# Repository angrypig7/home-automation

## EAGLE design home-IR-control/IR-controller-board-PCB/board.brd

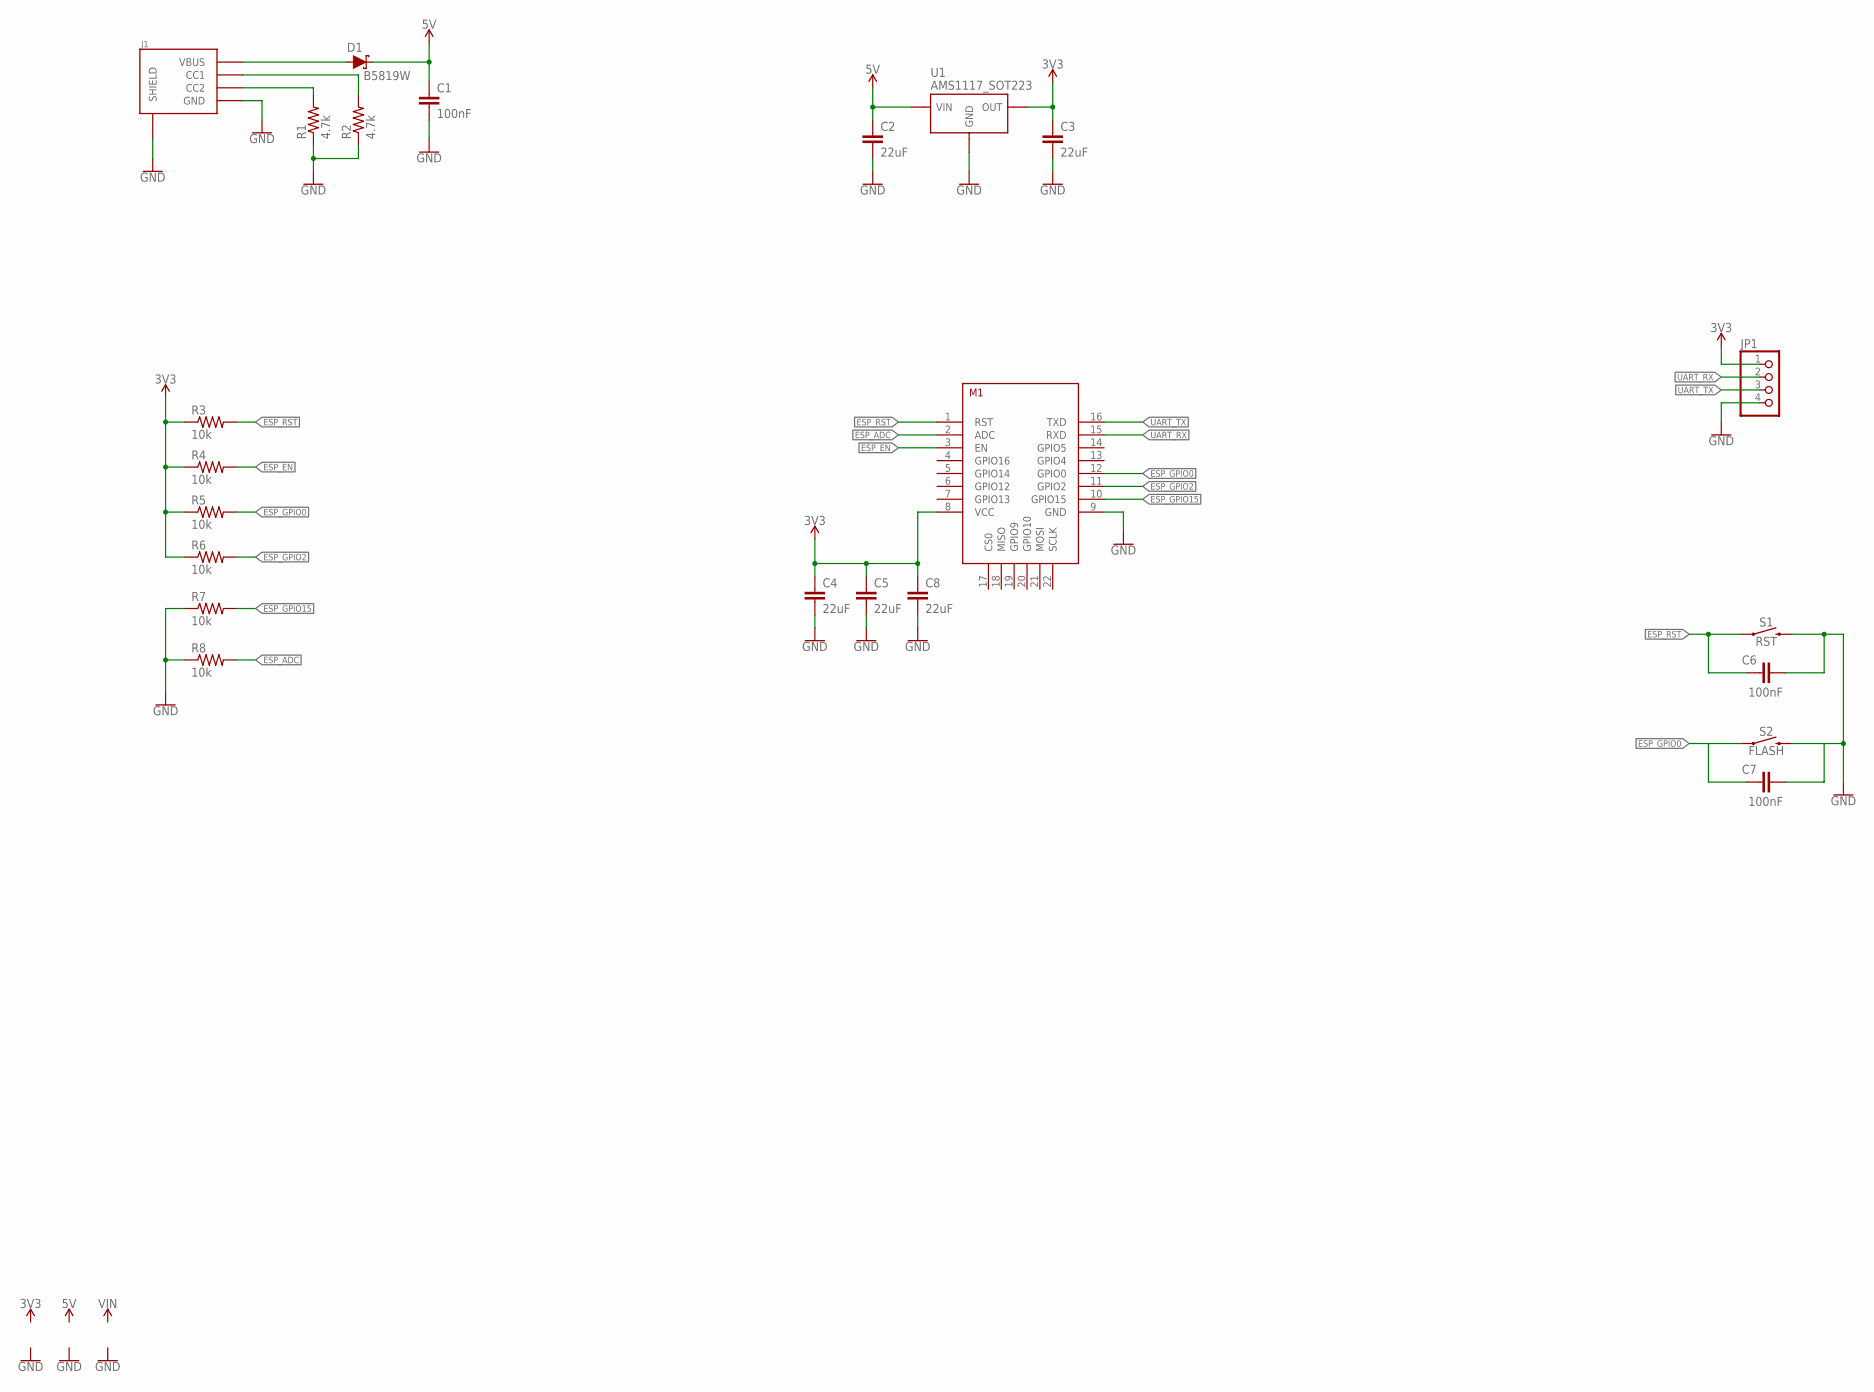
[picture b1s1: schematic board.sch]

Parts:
C1, C6, C7: 100nF; C0402; LCSC C1525
C2, C3, C4, C5, C8: 22uF; C0805; LCSC C45783
D1: B5819W; SOD-123; LCSC C8598
J1: USB-TYPE-C-31-M-17
JP1: PINHD-1X4; 1X04
M1: ESP8266-12E; ESP8266-ESP12E
R1, R2: 4.7k; R0402; LCSC C25900
R3, R4, R5, R6, R7, R8: 10k; R0402
S1: RST; TACTILE_SWITCH_SMD_3.0X4.0MM; LCSC C720477
S2: FLASH; TACTILE_SWITCH_SMD_3.0X4.0MM; LCSC C720477
U1: AMS1117_SOT223; SOT-223; LCSC C6186

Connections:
3V3: C3.1, C4.1, C5.1, C8.1, JP1.1, M1.8 (VCC), R3.1, R4.1, R5.1, R6.1, U1.2 (OUT), U1.4 (OUT)
5V: C1.1, C2.1, D1.C, U1.3 (VIN)
5V_IN1: D1.A, J1.VBUS, J1.VBUS_2 (VBUS)
ESP_ADC: M1.2 (ADC), R8.2
ESP_EN: M1.3 (EN), R4.2
ESP_GPIO0: M1.12 (GPIO0), R5.2, S2.1
ESP_GPIO2: M1.11 (GPIO2), R6.2
ESP_GPIO15: M1.10 (GPIO15), R7.2
ESP_RST: C6.1, M1.1 (RST), R3.2, S1.1
ESP_RST1: C7.1
GND: C1.2, C2.2, C3.2, C4.2, C5.2, C6.2, C8.2, J1.GND, J1.GND_2 (GND), J1.SHLD-B1 (SHIELD), J1.SHLD-B2 (SHIELD), J1.SHLD-B3 (SHIELD), J1.SHLD-B4 (SHIELD), J1.SHLD-T1 (SHIELD), J1.SHLD-T2 (SHIELD), J1.SHLD-T3 (SHIELD), J1.SHLD-T4 (SHIELD), JP1.4, M1.9 (GND), R1.1, R2.1, R7.1, R8.1, S1.2, S2.2, U1.1 (GND)
GND1: C7.2
unnamed: J1.CC1, R2.2
unnamed: J1.CC2, R1.2
UART_RX: JP1.2, M1.15 (RXD)
UART_TX: JP1.3, M1.16 (TXD)

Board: 2 copper layers, 23 parts (0 on the bottom side), 14 nets, no tracks yet.

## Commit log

2021-01-21 pics
2021-01-21 gitignore
2021-01-22 merged home-garden-automation repo
2021-01-27 change timer widget to time input - in progress
2021-01-29 fixed timer control
2021-02-12 IR controller PCB init
2021-02-26 PCB update
2021-03-28 Blynk to NTP
